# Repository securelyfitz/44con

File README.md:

44CON 2014 Badge
================

Based on the Dangerous Prototypes Bus Pirate V3c

Summary of changes:
-------------------
- changed PCB outline in dp_pcb.lbr
- added 44CON text in 44context.lbr
- added 1.8v LDO for using cpld without FTDI
- added LEDs and resistors on JP2 spare pins
- added 5x7mm Oscillator on pin 28
- added solder jumper near vtarget jumper

PCB Files
---------
* .sch and .brd: eagle schematic and board files 
* .lbr: eagle libraries for board outline and text items 
* .G* and .TXT: gerber files for fabricating board

CPLD Files
----------
* conled.v defines led flashing logic
* conled.v defines I/O pin assignments
* conled.jed xilinx bitstream file
* default.svf and default.xsvf bistream in generic format

Build options:
-------------
1. Generic USB Blaster for JTAG OCD, programming, and testing
1. Bare minimum CPLD build for flashing lights
1. Bare minimum CPLD build for cheap glitching

USB Blaster Build:
-----------------
see details on dangerous prototypes website:
http://dangerousprototypes.com/docs/Bus_Blaster_v3_design_overview

Flashy Light Build:
------------------

parts:
------
* CR2032 battery
* xilinx xc2c32a CPLD
* lm3480 1.8v regulator (note pinout!!!)
* 3.3nF tantalum capacitor
* 0805 LED x5
* 0603 50 ohm resistor
* .1" header for programming
* 5x7mm 50mhz (ish) oscillator
* CR2032 holder

building:
--------
1. solder battery holder onto the back of the board between jp2 3.3v pin and a JTAG GND pin
1. solder over the solder jumper in the upper right corner of the board
1. solder lm3480 just below and in between the FTDI and CPLD chips
  * if you have an AP7313 the pinout is different, rotate it clockwise 120 degrees and solder it
1. solder the tantalum capacitor on C2 with + towards the top of the PCB
1. put the CR2032 in and test that you have 3ish  volts on the 3.3v pins and 1.8 volts on the right lead of the regulator
1. remove the CR2032
1. solder the oscillator in the bottom right. Pin1 is in the far bottom right
1. solder the CPLD in place. Pin1 goes up
1. solder the resistors in place between the 2014 on the bottom. Resistors go on the upper pads
1. solder the LEDs below the resistors. + is to the left, - to the right
1. put the CR2032 back in and test for output from pin 3 of the oscillator (top left) with a multemeter to make sure it's not 0v
1. using a jtag programmer - Xilinx cable, Bus blaster, or a bus pirate in SVF mode - configure your CPLD and watch lights flash!

troubleshooting:
---------------
* if you can't recognize/configure the CPLD or lights are very dim, it could be a power issue. double check the 1.8v regulator and that the capacior is in the right direction.
* if the LEDs go on but don't flash, check your oscillator

Glitching build:
----------------
same as flashy light build, though LEDS are optional. WIP to use it for glitching arduinos and/or XBOX360s

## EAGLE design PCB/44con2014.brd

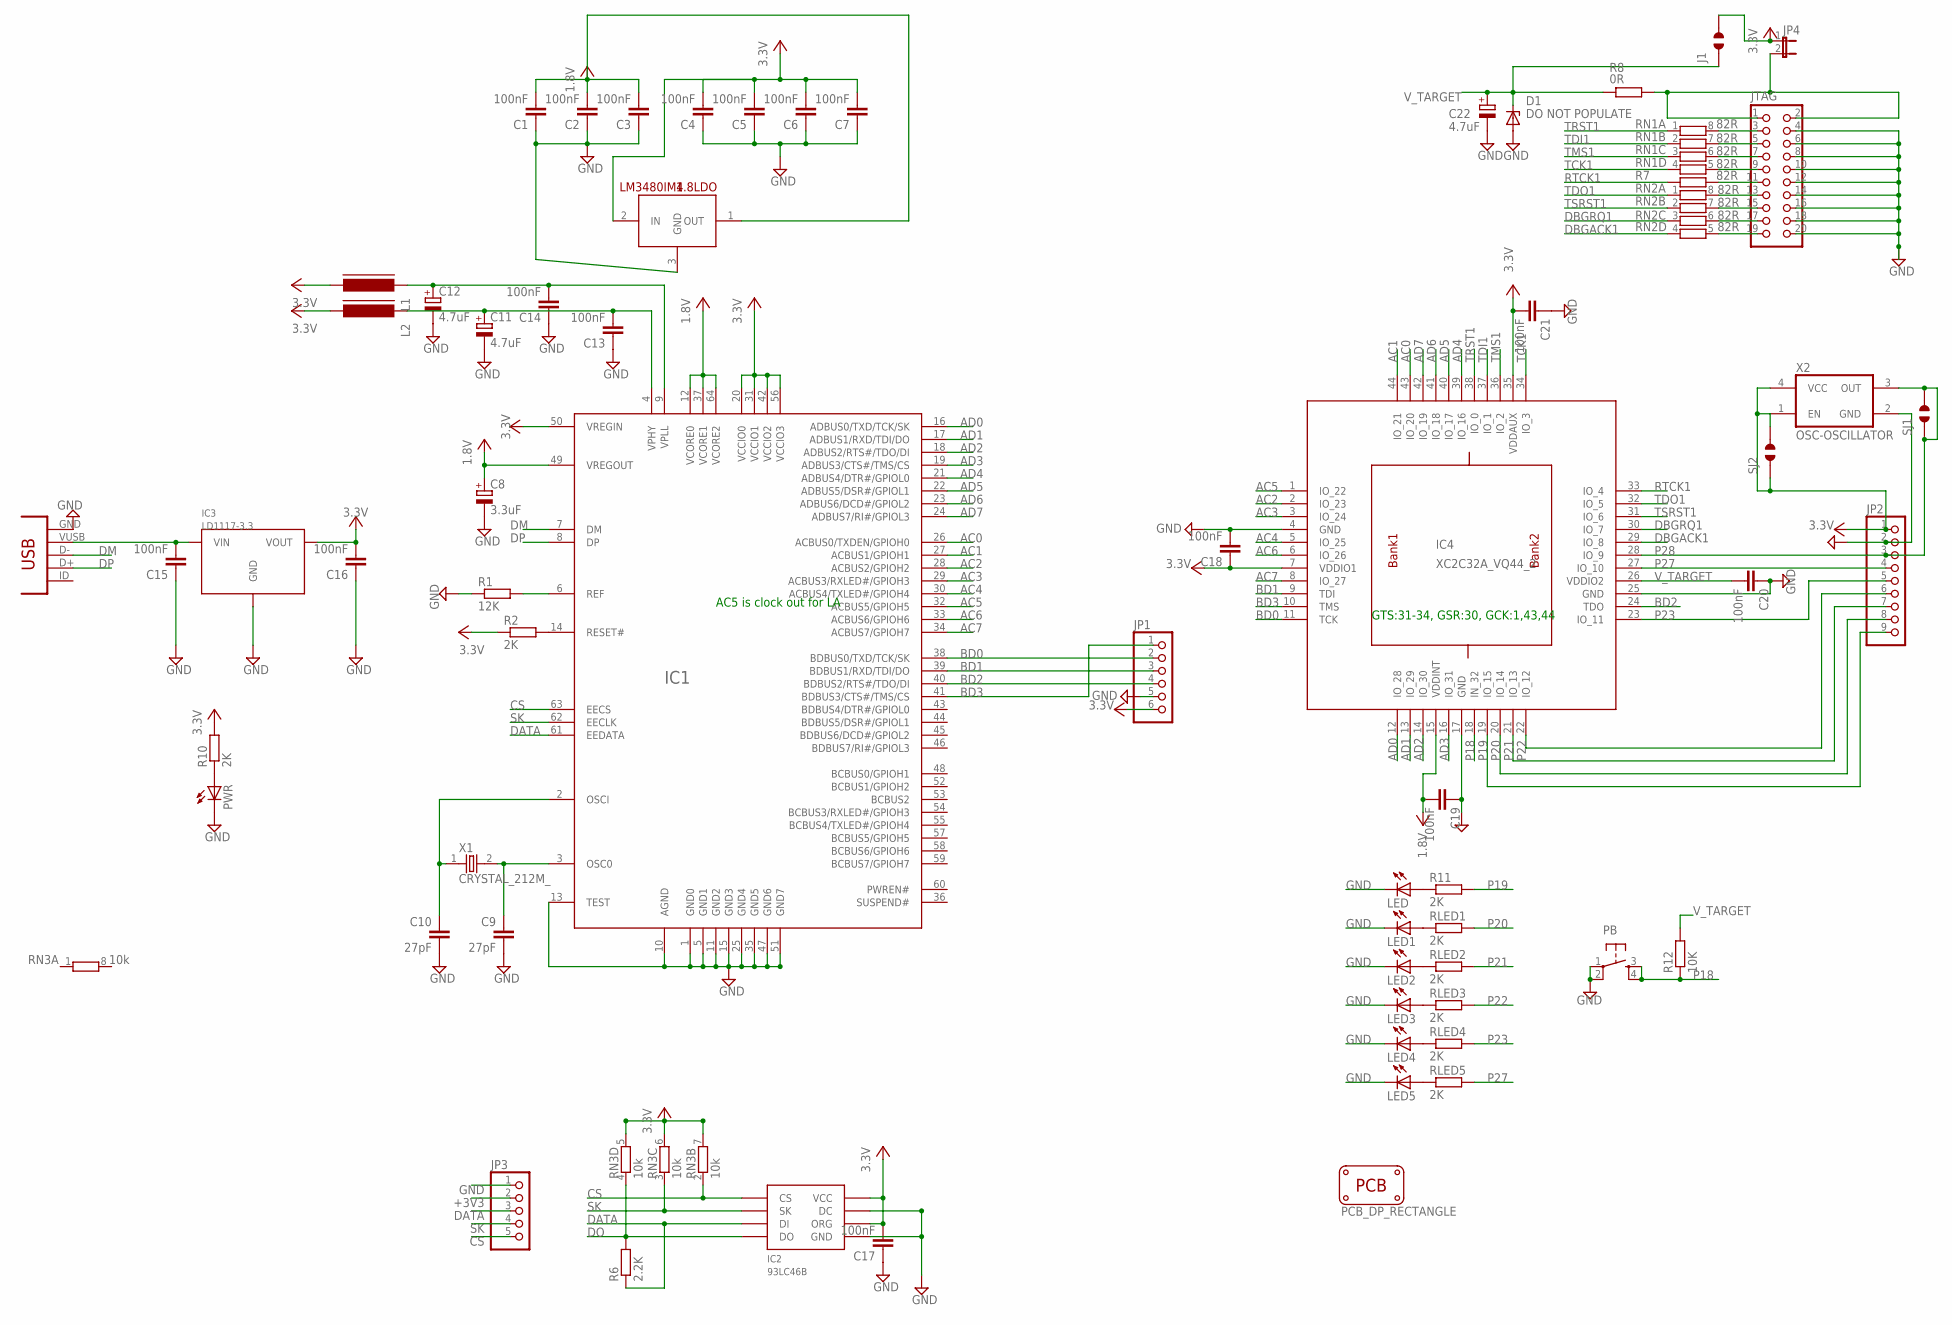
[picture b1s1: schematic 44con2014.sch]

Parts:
1.8LDO: LM3480IM4; SOT23-3
C1, C2, C3, C4, C5, C6, C7, C13, C14, C15, C16, C17, C18, C19, C20, C21: 100nF; C603
C8: 3.3uF; SMC_A
C9, C10: 27pF; C603
C11, C12, C22: 4.7uF; SMC_A
D1: DO NOT POPULATE; SOD-123
IC1: FT2232H; LQFP64
IC2: 93LC46B; SOIC8
IC3: LD1117-3.3; SOT223
IC4: XC2C32A_VQ44_2; VQ44
J1: JUMPER_SOLDER_1X2
JP1: PINHD-1X6; 1X06
JP2: PINHD-1X9; 1X09
JP3: PINHD-1X5; 1X05
JP4: JP1EJP; 1X02
JTAG: CON_HEADER_2X10-SHROUDED; PINSHRD_PTH_2X10
L1, L2: FERRITE_BEAD603; FB603
LED, LED1, LED2, LED3, LED4, LED5: LED805; LED-805
PB: SW-SMD-SMALL; TACT_SWITCH_SMALL
PCB3: PCB_DP_RECTANGLE; 44CON2014
PWR: LEDCHIPLED_0805; CHIPLED_0805
R1: 12K; R603
R2, R10, R11: 2K; R603
R6: 2.2K; R603
R7: 82R; R603
R8: 0R; R1206
R12: 10K; R603
RLED1, RLED2, RLED3, RLED4, RLED5: 2K; R603
RN1, RN2: 82R; RN8P-4R-CRA06S
RN3: 10k; RN8P-4R-CRA06S
SJ1, SJ2: JUMPER_SOLDER_1X2
USB: CON-USB-MINI-BUSB1; CONN_USB_MINI-B
X1: CRYSTAL_212M_; XTAL_4X6
X2: OSC-OSCILLATOR; OSCILLATOR_7X5_SMD

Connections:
1.8V: 1.8LDO.1 (OUT), C1.2, C2.2, C3.2, C8.+, C19.2, IC1.12 (VCORE0), IC1.37 (VCORE1), IC1.49 (VREGOUT), IC1.64 (VCORE2), IC4.15 (VDDINT)
+3V3: 1.8LDO.2 (IN), C4.2, C5.2, C6.2, C7.2, C16.2, C17.2, C18.1, C21.2, IC1.20 (VCCIO0), IC1.31 (VCCIO1), IC1.42 (VCCIO2), IC1.50 (VREGIN), IC1.56 (VCCIO3), IC2.6 (ORG), IC2.8 (VCC), IC3.2 (VOUT), IC4.7 (VDDIO1), IC4.35 (VDDAUX), J1.2, JP1.6, JP2.1, JP3.2, JP4.1, L1.2, L2.2, R2.1, R10.2, RN3.5 (2), RN3.6 (2), RN3.7 (2), SJ2.1, SJ2.2, X2.1 (EN), X2.4 (VCC)
AC0: IC1.26 (ACBUS0/TXDEN/GPIOH0), IC4.43 (IO_20)
AC1: IC1.27 (ACBUS1/GPIOH1), IC4.44 (IO_21)
AC2: IC1.28 (ACBUS2/GPIOH2), IC4.2 (IO_23)
AC3: IC1.29 (ACBUS3/RXLED#/GPIOH3), IC4.3 (IO_24)
AC4: IC1.30 (ACBUS4/TXLED#/GPIOH4), IC4.5 (IO_25)
AC5: IC1.32 (ACBUS5/GPIOH5), IC4.1 (IO_22)
AC6: IC1.33 (ACBUS6/GPIOH6), IC4.6 (IO_26)
AC7: IC1.34 (ACBUS7/GPIOH7), IC4.8 (IO_27)
AD0: IC1.16 (ADBUS0/TXD/TCK/SK), IC4.12 (IO_28)
AD1: IC1.17 (ADBUS1/RXD/TDI/DO), IC4.13 (IO_29)
AD2: IC1.18 (ADBUS2/RTS#/TDO/DI), IC4.14 (IO_30)
AD3: IC1.19 (ADBUS3/CTS#/TMS/CS), IC4.16 (IO_31)
AD4: IC1.21 (ADBUS4/DTR#/GPIOL0), IC4.39 (IO_16)
AD5: IC1.22 (ADBUS5/DSR#/GPIOL1), IC4.40 (IO_17)
AD6: IC1.23 (ADBUS6/DCD#/GPIOL2), IC4.41 (IO_18)
AD7: IC1.24 (ADBUS7/RI#/GPIOL3), IC4.42 (IO_19)
BD0: IC1.38 (BDBUS0/TXD/TCK/SK), IC4.11 (TCK), JP1.2
BD1: IC1.39 (BDBUS1/RXD/TDI/DO), IC4.9 (TDI), JP1.3
BD2: IC1.40 (BDBUS2/RTS#/TDO/DI), IC4.24 (TDO), JP1.4
BD3: IC1.41 (BDBUS3/CTS#/TMS/CS), IC4.10 (TMS), JP1.1
CS: IC1.63 (EECS), IC2.1 (CS), JP3.5, RN3.2 (1)
DATA: IC1.61 (EEDATA), IC2.3 (DI), JP3.3, R6.1
DBGACK1: IC4.29 (IO_8), RN2.4 (1)
DBGRQ1: IC4.30 (IO_7), RN2.3 (1)
DM: IC1.7 (DM), USB.D-
DO: IC2.4 (DO), R6.2, RN3.4 (1)
DP: IC1.8 (DP), USB.D+
GND: 1.8LDO.3 (GND), C1.1, C2.1, C3.1, C4.1, C5.1, C6.1, C7.1, C8.-, C9.2, C10.2, C11.-, C12.-, C13.1, C14.1, C15.1, C16.1, C17.1, C18.2, C19.1, C20.1, C21.1, C22.-, D1.A, IC1.1 (GND0), IC1.5 (GND1), IC1.10 (AGND), IC1.11 (GND2), IC1.13 (TEST), IC1.15 (GND3), IC1.25 (GND4), IC1.35 (GND5), IC1.47 (GND6), IC1.51 (GND7), IC2.5 (GND), IC2.7 (DC), IC3.1 (GND), IC4.4 (GND), IC4.17 (GND), IC4.25 (GND), JP1.5, JP2.2, JP3.1, JTAG.4, JTAG.6, JTAG.8, JTAG.10, JTAG.12, JTAG.14, JTAG.16, JTAG.18, JTAG.20, LED.C, LED1.C, LED2.C, LED3.C, LED4.C, LED5.C, PB.1, PB.2, PWR.C, R1.1, USB.GND, X2.2 (GND)
unnamed: C9.1, IC1.3 (OSC0), X1.2
unnamed: C10.1, IC1.2 (OSCI), X1.1
unnamed: IC1.14 (RESET#), R2.2
unnamed: IC1.6 (REF), R1.2
unnamed: C15.2, IC3.3 (VIN), USB.VUSB
unnamed: PWR.A, R10.1
unnamed: JTAG.3, RN1.8 (2)
unnamed: LED.A, R11.1
unnamed: JTAG.5, RN1.7 (2)
unnamed: JTAG.7, RN1.6 (2)
unnamed: JTAG.9, RN1.5 (2)
unnamed: JTAG.11, R7.2
unnamed: JTAG.13, RN2.8 (2)
unnamed: JTAG.15, RN2.7 (2)
unnamed: JTAG.17, RN2.6 (2)
unnamed: JTAG.19, RN2.5 (2)
unnamed: LED1.A, RLED1.1
unnamed: LED2.A, RLED2.1
unnamed: LED3.A, RLED3.1
unnamed: LED4.A, RLED4.1
unnamed: LED5.A, RLED5.1
P18: IC4.18 (IN_32), PB.3, PB.4, R12.1
P19: IC4.19 (IO_15), JP2.9, R11.2
P20: IC4.20 (IO_14), JP2.8, RLED1.2
P21: IC4.21 (IO_13), JP2.7, RLED2.2
P22: IC4.22 (IO_12), JP2.6, RLED3.2
P23: IC4.23 (IO_11), JP2.5, RLED4.2
P27: IC4.27 (IO_10), JP2.4, RLED5.2
P28: IC4.28 (IO_9), JP2.3, SJ1.1, SJ1.2, X2.3 (OUT)
RTCK1: IC4.33 (IO_4), R7.1
SK: IC1.62 (EECLK), IC2.2 (SK), JP3.4, RN3.3 (1)
TCK1: IC4.34 (IO_3), RN1.4 (1)
TDI1: IC4.37 (IO_1), RN1.2 (1)
TDO1: IC4.32 (IO_5), RN2.1
TMS1: IC4.36 (IO_2), RN1.3 (1)
TRST1: IC4.38 (IO_0), RN1.1
TSRST1: IC4.31 (IO_6), RN2.2 (1)
VPHY: C11.+, C13.2, IC1.4 (VPHY), L2.1
VPLL: C12.+, C14.2, IC1.9 (VPLL), L1.1
V_TARGET: C20.2, C22.+, D1.C, IC4.26 (VDDIO2), J1.1, R8.1, R12.2
V_TARGET_UNREG: JP4.2, JTAG.1, JTAG.2, R8.2

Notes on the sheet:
GTS:31-34, GSR:30, GCK:1,43,44
AC5 is clock out for LA

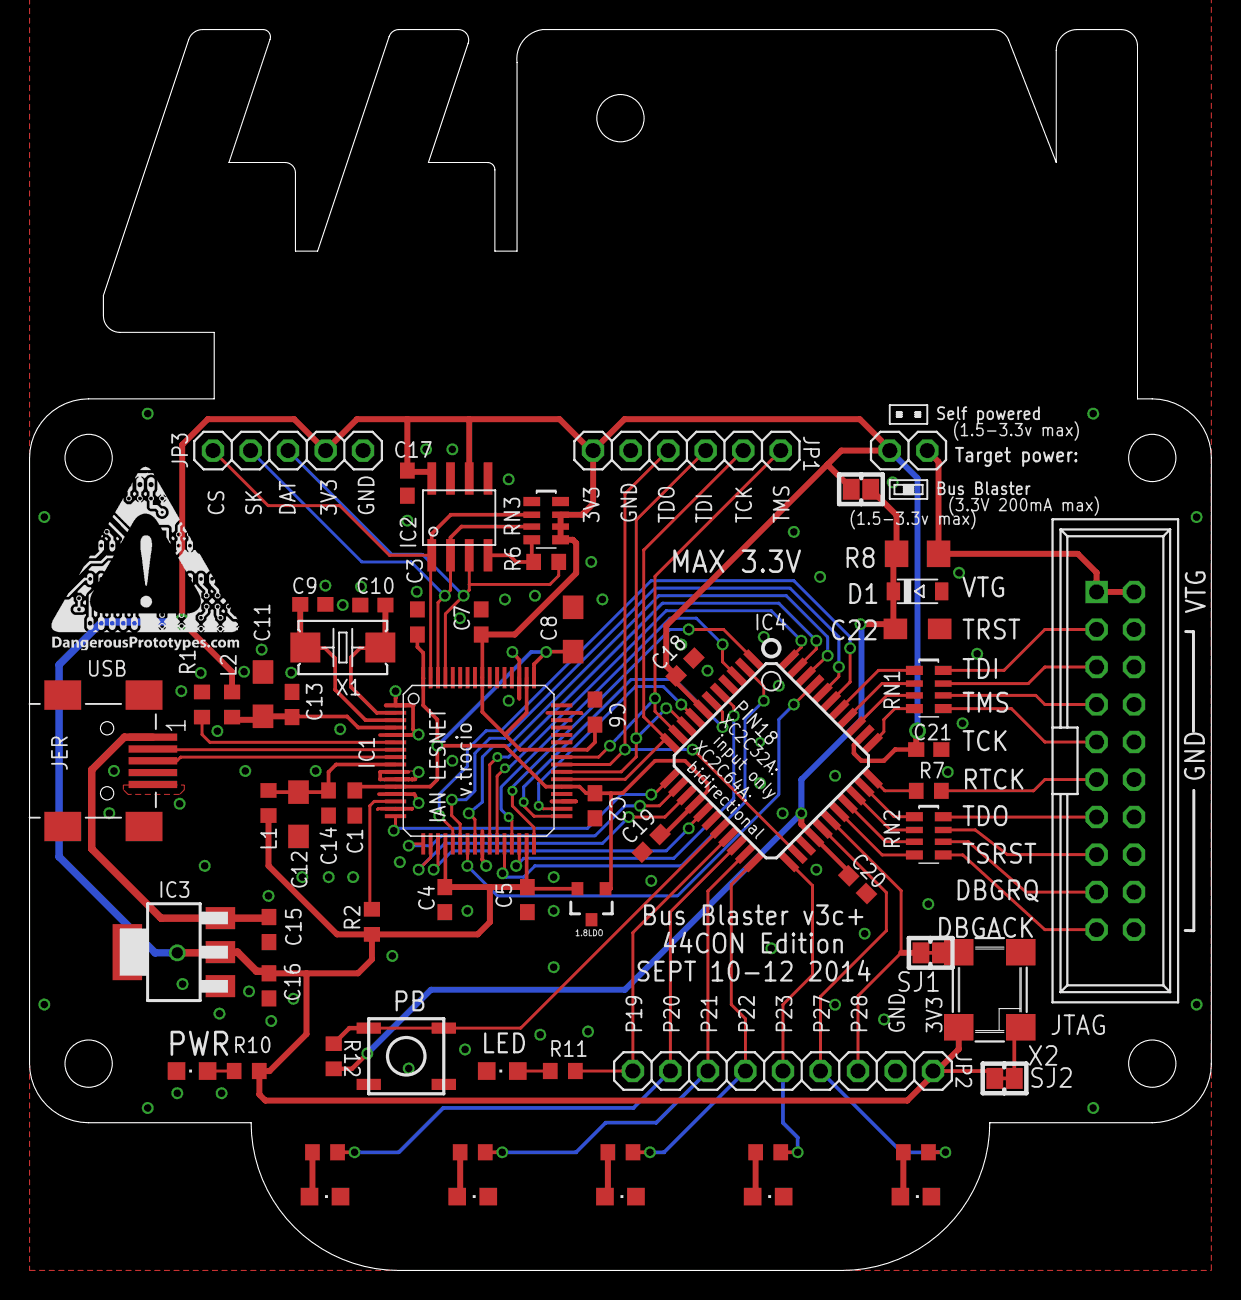
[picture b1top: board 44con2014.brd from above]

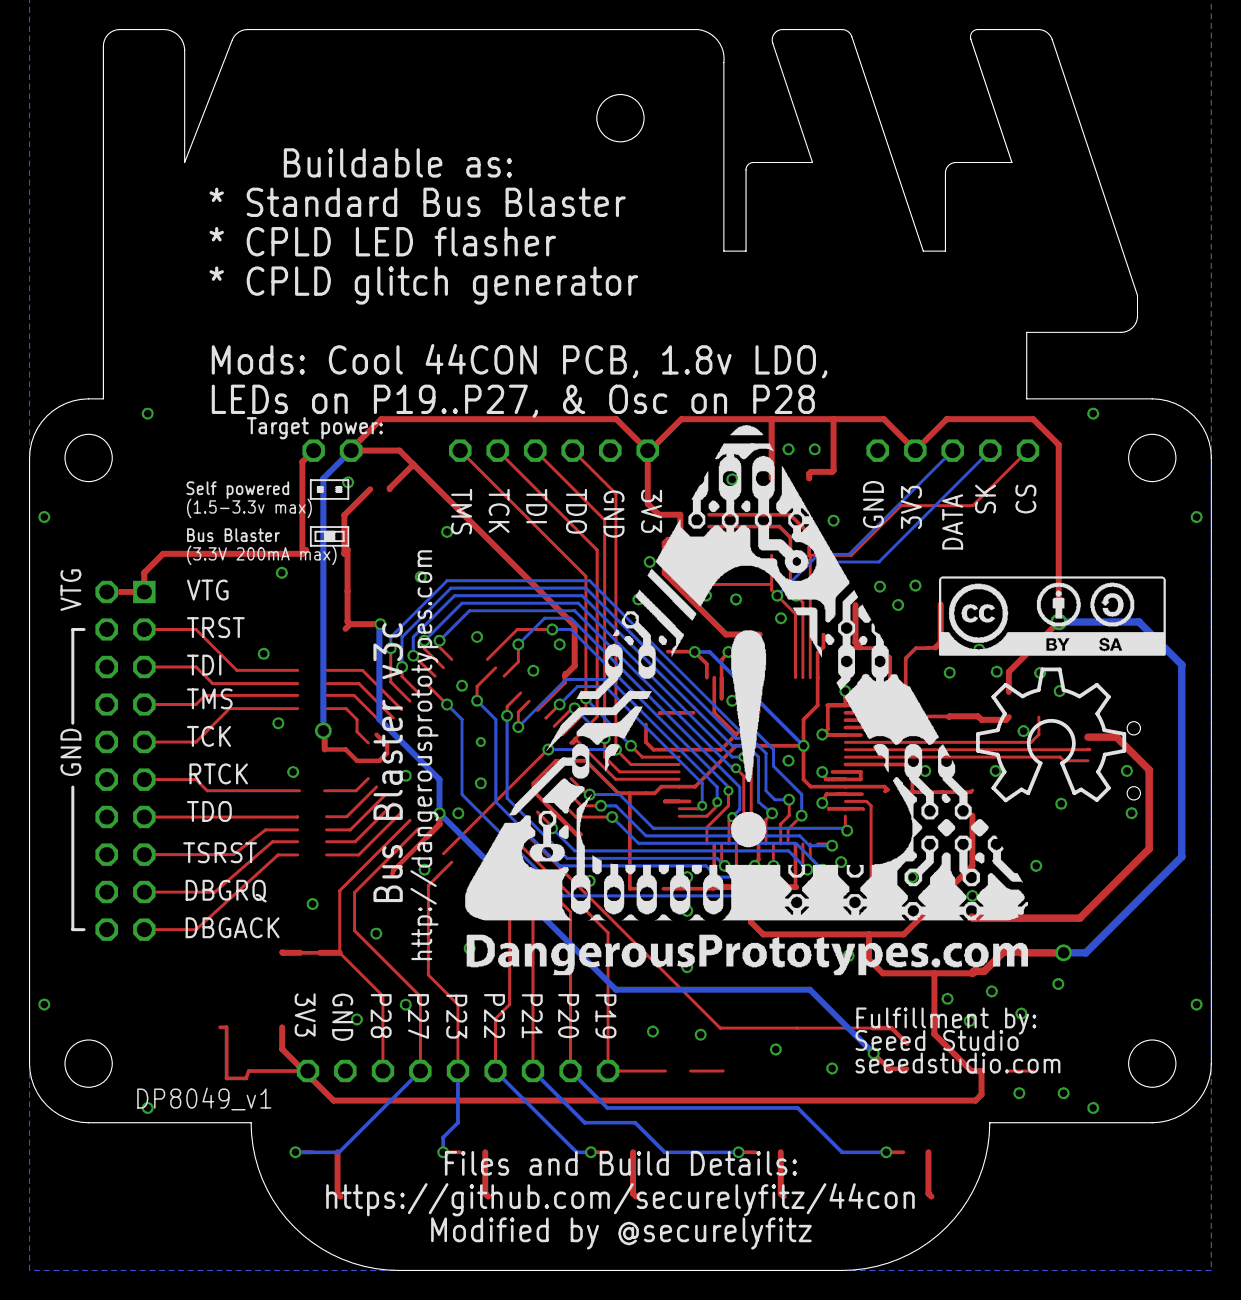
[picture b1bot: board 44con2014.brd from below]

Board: 2 copper layers, 80.0 x 84.0 mm, 76 parts (5 on the bottom side), 71 nets.

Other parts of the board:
U$1: DP_LOGO_ART_1.5X1.5
U$2: DP_LOGO_ART_0.5X0.5
U$3: CC-BY-SA
U$4: 44CON
U$5: OSHW_10X350_NOTEXT
U$6, U$9: adasdsd; JUMP2_DESC_ON
U$7, U$8: JUMP2_DESC_OFF
U$10: 2014

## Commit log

2014-09-11 initial commit of pcb files, CPLD files, and readme
2014-09-11 fixing readme formatting and adding pics
2014-09-11 image resize
2014-09-16 capitalizing 44CON

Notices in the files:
parts and their libraries:
SparkFun-PowerIC: Licensing: Creative Commons ShareAlike 4.0 International - https://creativecommons.org/licenses/by-sa/4.0
